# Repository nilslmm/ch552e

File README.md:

# ch552e
A simple PCB for the ch552e

I wanted to learn SMD soldering and PCB creation. That's why I came up with this small project.

The PCB comes with two LEDs. One Power indicator and one that can be programmed. One programmable button.
It has pads that can be bridged to enter bootloader mode.

# Usage
After getting the PCB manufactured and soldering all the components you can program it as you wish.

To program the ch552e using the Arduino IDE you need to add a Board Manager URL.
For this you go to File > Preferences and add ```https://raw.githubusercontent.com/DeqingSun/ch55xduino/ch55xduino/package_ch55xduino_mcs51_index.json```
After that you open the board manager and install 

# Example Code

```c
#include <USBHID.h>

const int statusLedPin = P1_4; 

void setup() {
  pinMode(statusLedPin, OUTPUT);
  USBInit();  
  
  // Delay for HID detection
  delay(2000);

  digitalWrite(statusLedPin, HIGH);
  Keyboard_print("supersecret");
  digitalWrite(statusLedPin, LOW);
}
void loop() {
}
```

Go to Tools and make sure you are using those settings:
Bootloader Pin: P3.6 (D+) pull-up
Clock Source: 16MHz (internal), 3.3v or 5v
Upload Method: USB
USB Settings: USER CODE w/ 148B USB (based on your use case you might want to use something else. For simple keystrokes this is the best. Do you own research for other use cases)

# BOM

| Amount | Component | Value | Size | Price | Package Size | Link
|:---|:---:|:---:|:---:|:---:|:---:|---:|
| 2x | Capacitor | 100nF |  0805 | 0.39 EUR | 20 | https://www.lcsc.com/product-detail/C49678.html
| 1x | LED | Green |  0805 | 0.59 EUR | 100 | https://www.lcsc.com/product-detail/C19273151.html
| 1x | LED | Orange |  0805 | 0.82 EUR | 50 | https://www.lcsc.com/product-detail/C28310440.html
| 2x | Resistor | 330Ohm |  0805 | 0.54 EUR | 100 | https://www.lcsc.com/product-detail/C17630.html
| 1x | Resistor | 1.5kOhm |  0805 | 0.32 EUR | 100 | https://www.lcsc.com/product-detail/C2907216.html
| 1x | Tac Switch | SKQGABE010 | / | 1.24 EUR | 10 | https://www.lcsc.com/product-detail/C115351.html
| 1x | Chip | CH552E | / | 0.57 EUR | 1 | https://www.lcsc.com/product-detail/C967938.html
| 1x| PCB | / | / | 5.50 EUR | 10 | https://jlcpcb.com/

Total costs: 9.97 EUR

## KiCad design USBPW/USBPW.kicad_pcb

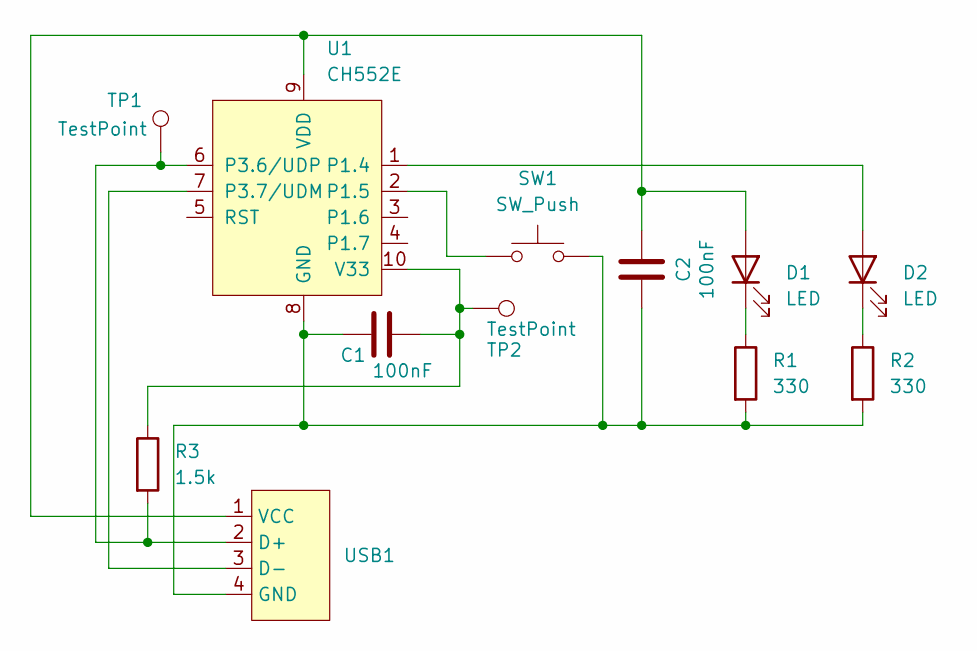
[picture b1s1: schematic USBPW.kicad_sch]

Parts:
C1, C2: 100nF; C_0805_2012Metric
D1, D2: LED; LED_0805_2012Metric
R1, R2: 330; R_0805_2012Metric
R3: 1.5k; R_0805_2012Metric
SW1: SW_Push; SW_SPST_SKQG_WithStem
TP1, TP2: TestPoint; TestPoint_Pad_D1.0mm
U1: CH552E; TSSOP-10_3x3mm_P0.5mm
USB1: PCB_USB_CONNECTOR

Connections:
unnamed: C2.2, D1.2 (A), U1.9 (VDD), USB1.1 (VCC)
unnamed: D1.1 (K), R1.1
unnamed: D2.2 (A), U1.1 (P1.4)
unnamed: D2.1 (K), R2.1
unnamed: C1.1, C2.1, R1.2, R2.2, SW1.2, U1.8 (GND), USB1.4 (GND)
unnamed: SW1.1, U1.2 (P1.5)
unnamed: R3.2, TP1.1 (1_1), U1.6 (P3.6/UDP), USB1.2 (D+)
unnamed: U1.7 (P3.7/UDM), USB1.3 (D-)
unnamed: C1.2, R3.1, TP2.1 (1_1), U1.10 (V33)

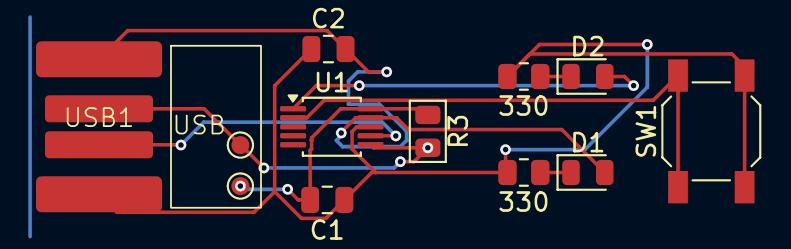
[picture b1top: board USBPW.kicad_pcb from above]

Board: 2 copper layers, 12 parts (0 on the bottom side), 9 nets.

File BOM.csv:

"Reference","Qty","Value","DNP","Exclude from BOM","Exclude from Board","Exclude from Simulation","Exclude from Position Files","Footprint","Datasheet"
"C1,C2","2","100nF","","","","","${EXCLUDE_FROM_POS_FILES}","Capacitor_SMD:C_0805_2012Metric",""
"D1,D2","2","LED","","","","","${EXCLUDE_FROM_POS_FILES}","LED_SMD:LED_0805_2012Metric",""
"R1,R2","2","330","","","","","${EXCLUDE_FROM_POS_FILES}","Resistor_SMD:R_0805_2012Metric",""
"R3","1","1.5k","","","","","${EXCLUDE_FROM_POS_FILES}","Resistor_SMD:R_0805_2012Metric",""
"SW1","1","SW_Push","","","","","${EXCLUDE_FROM_POS_FILES}","Button_Switch_SMD:SW_SPST_SKQG_WithStem",""
"TP1,TP2","2","TestPoint","","","","","${EXCLUDE_FROM_POS_FILES}","TestPoint:TestPoint_Pad_D1.0mm",""
"U1","1","CH552E","","","","","${EXCLUDE_FROM_POS_FILES}","Package_SO:TSSOP-10_3x3mm_P0.5mm",""
